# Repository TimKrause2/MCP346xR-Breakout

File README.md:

# MCP346xR-Breakout

## License

[![CC BY 4.0][cc-by-shield]][cc-by]

**MCP346xR-Breakout** © 2026 by **Timothy Krause** is licensed under [Creative Commons Attribution 4.0 International][cc-by].

[cc-by]: http://creativecommons.org
[cc-by-shield]: https://shields.io

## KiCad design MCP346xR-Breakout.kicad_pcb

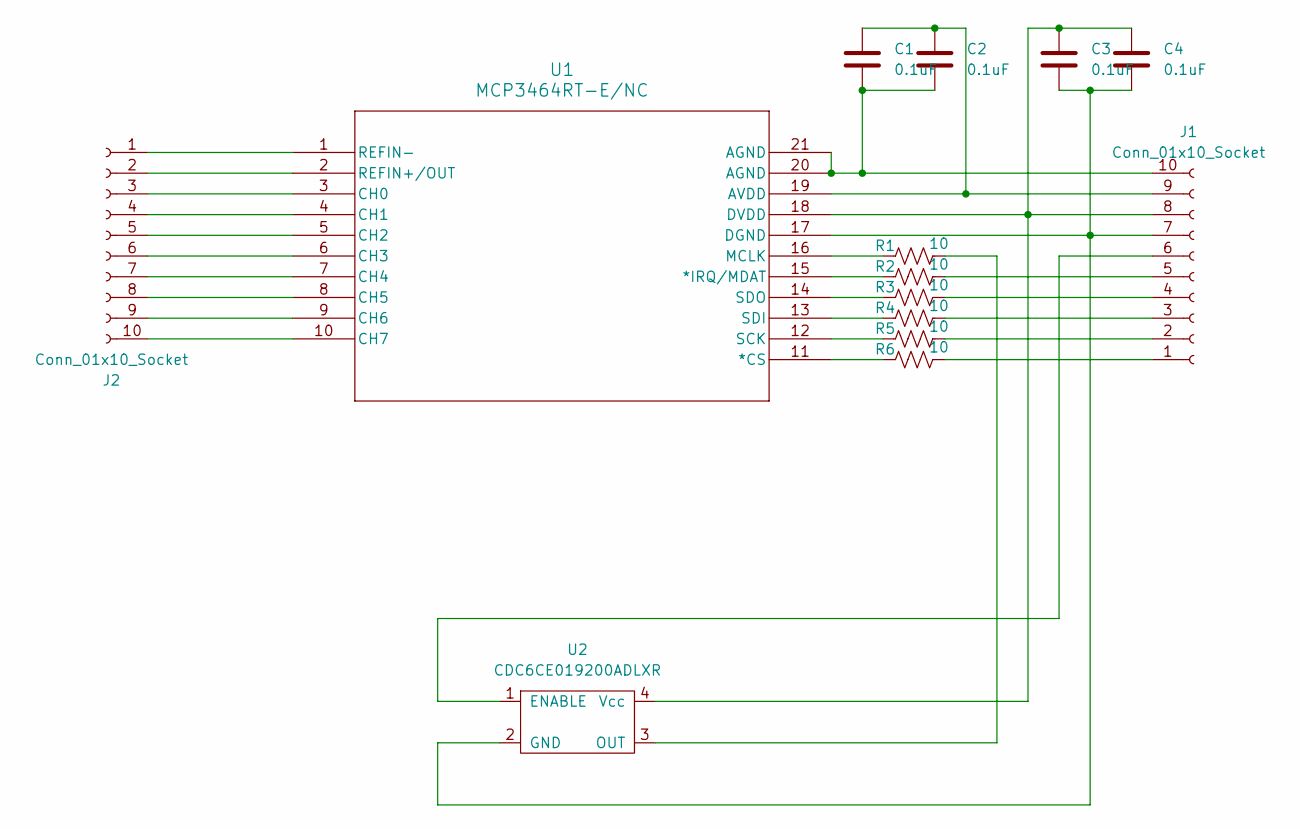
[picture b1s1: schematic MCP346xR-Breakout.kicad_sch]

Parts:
C1, C2, C3, C4: 0.1uF; C_0603_1608Metric
J1, J2: Conn_01x10_Socket; PinHeader_1x10_P2.54mm_Vertical
R1, R2, R3, R4, R5, R6: 10; R_0603_1608Metric
U1: MCP3464RT-E/NC; UQFN20_NC_MCH
U2: CDC6CE019200ADLXR; DLX0004A

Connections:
unnamed: J1.1, R6.2
unnamed: J1.2, R5.2
unnamed: J1.3, R4.2
unnamed: J1.4, R3.2
unnamed: J1.5, R2.2
unnamed: J1.6, U2.1 (ENABLE)
unnamed: C3.2, C4.2, J1.7, U1.17 (DGND), U2.2 (GND)
unnamed: C3.1, C4.1, J1.8, U1.18 (DVDD), U2.4 (Vcc)
unnamed: C1.1, C2.1, J1.9, U1.19 (AVDD)
unnamed: C1.2, C2.2, J1.10, U1.20 (AGND), U1.21 (AGND)
unnamed: J2.1, U1.1 (REFIN-)
unnamed: J2.2, U1.2 (REFIN+/OUT)
unnamed: J2.3, U1.3 (CH0)
unnamed: J2.4, U1.4 (CH1)
unnamed: J2.5, U1.5 (CH2)
unnamed: J2.6, U1.6 (CH3)
unnamed: J2.7, U1.7 (CH4)
unnamed: J2.8, U1.8 (CH5)
unnamed: J2.9, U1.9 (CH6)
unnamed: J2.10, U1.10 (CH7)
unnamed: R6.1, U1.11 (*CS)
unnamed: R2.1, U1.15 (*IRQ/MDAT)
unnamed: R1.1, U1.16 (MCLK)
unnamed: R5.1, U1.12 (SCK)
unnamed: R4.1, U1.13 (SDI)
unnamed: R3.1, U1.14 (SDO)
unnamed: R1.2, U2.3 (OUT)

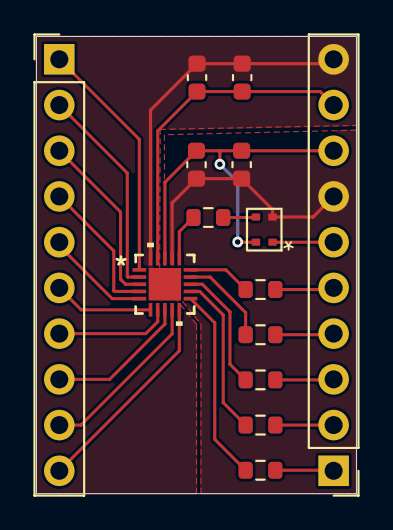
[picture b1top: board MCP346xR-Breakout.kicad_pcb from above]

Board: 2 copper layers, 17.8 x 25.4 mm, 14 parts (0 on the bottom side), 27 nets.
